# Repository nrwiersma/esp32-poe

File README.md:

# ESP32 PoE

`ESP32 PoE` is an ESP32 dev-kit with a W5500 LAN with PoE.

Features:

* W5500 Ethernet
* PoE (Power over Ethernet) 802.3af 7W
* ESP32 S3 WROOM-1

## Tasmota Configuration

To configure Tasmota for the ESP32 PoE board, you can use the following template:

```
{"NAME":"ESP32PoE","GPIO":[0,1,1,1,1,1,1,1,0,5536,5600,704,672,736,5568,1,1,1,1,1,1,0,0,0,1,1,1,1,1,1,1,1,1,1,1,1,1,1],"FLAG":0,"BASE":1}
```

and set the `EthType` option to `8`.

Optionally you can disable WiFi by setting `Wifi` option to `0` in the consoleSt.

## BOM

See the [Interactive BOM](https://htmlpreview.github.io/?https://github.com/nrwiersma/esp32-poe/blob/main/bom/ibom.html) [(provided by InteractiveHtmlBom)
](https://github.com/openscopeproject/InteractiveHtmlBom).

## Why

When dealing with IoT devices, you often want to place them in locations where power outlets are not readily available. 
Power over Ethernet (PoE) allows you to power devices through the same Ethernet cable used for data transmission, 
simplifying installation and reducing cable clutter. It also allows for centralized power management, 
making it easier to monitor and control the power supply to multiple devices.

## Changelog

#### v0.1.0

* Initial schematic and board

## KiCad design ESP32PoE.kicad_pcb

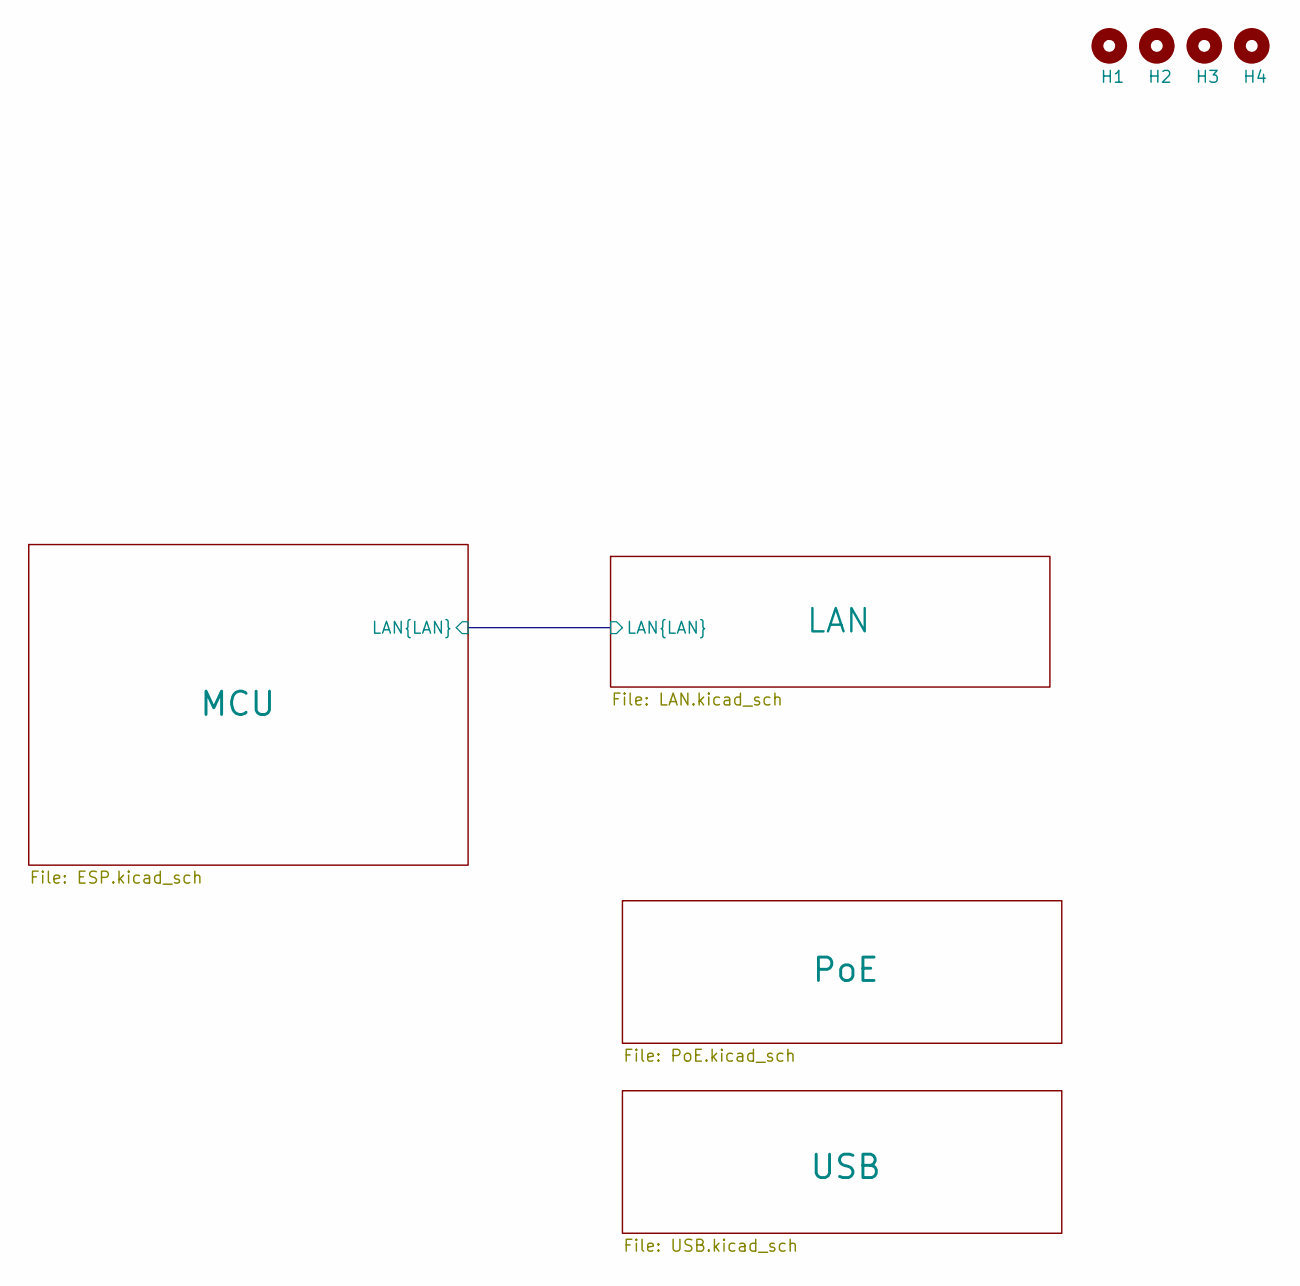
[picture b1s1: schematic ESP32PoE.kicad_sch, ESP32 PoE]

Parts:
H1, H2, H3, H4: MountingHole; MountingHole_2.2mm_M2

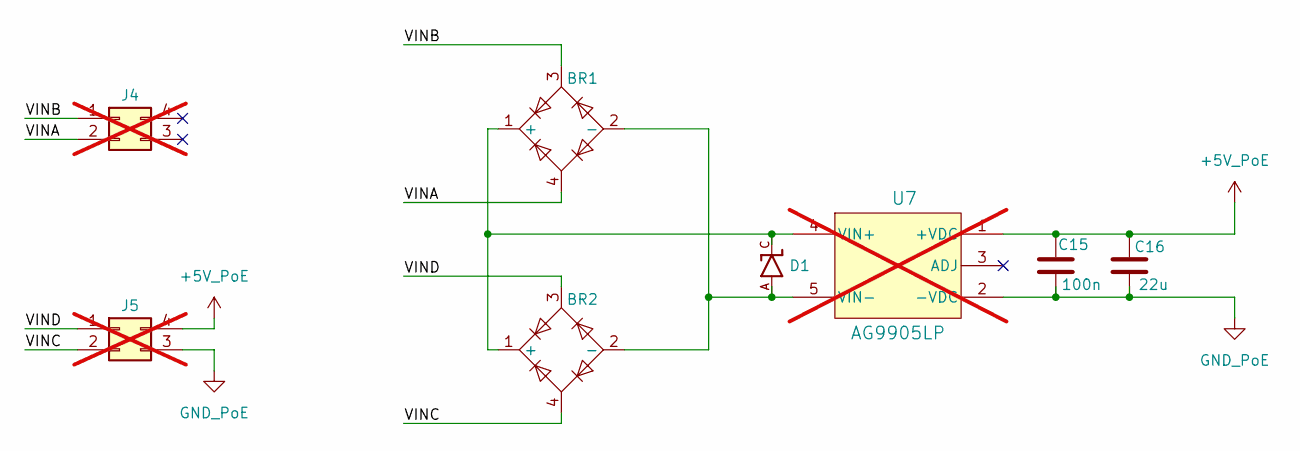
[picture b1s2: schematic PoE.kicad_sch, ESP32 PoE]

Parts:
BR1, BR2: MB110S; MPN MB110S; JLCPCB Part # C94545
C15: 100n; C_0402_1005Metric; MPN CL05B104KO5NNNC; JLCPCB Part # C1525
C16: 22u; C_0805_2012Metric; MPN CL21A226KPCLRNC; JLCPCB Part # C318688
D1: SMAJ58A; D_SMAJ58A; MPN SMAJ58A; JLCPCB Part # C151246
J4, J5: Conn_02x02_Counter_Clockwise; PinSocket_2x02_P2.54mm_Vertical; not fitted
U7: AG9905LP; POE_AG9905LP; MPN AG9905LP; not fitted

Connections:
+5V_PoE: C15.2, C16.1, J5.4, U7.1 (+VDC)
/PoE/VINA: BR1.4, J4.2
/PoE/VINB: BR1.3, J4.1
/PoE/VINC: BR2.4, J5.2
/PoE/VIND: BR2.3, J5.1
GND_PoE: C15.1, C16.2, J5.3, U7.2 (-VDC)
unnamed: BR1.1 (+), BR2.1 (+), D1.C, U7.4 (VIN+)
unnamed: BR1.2 (-), BR2.2 (-), D1.A, U7.5 (VIN-)

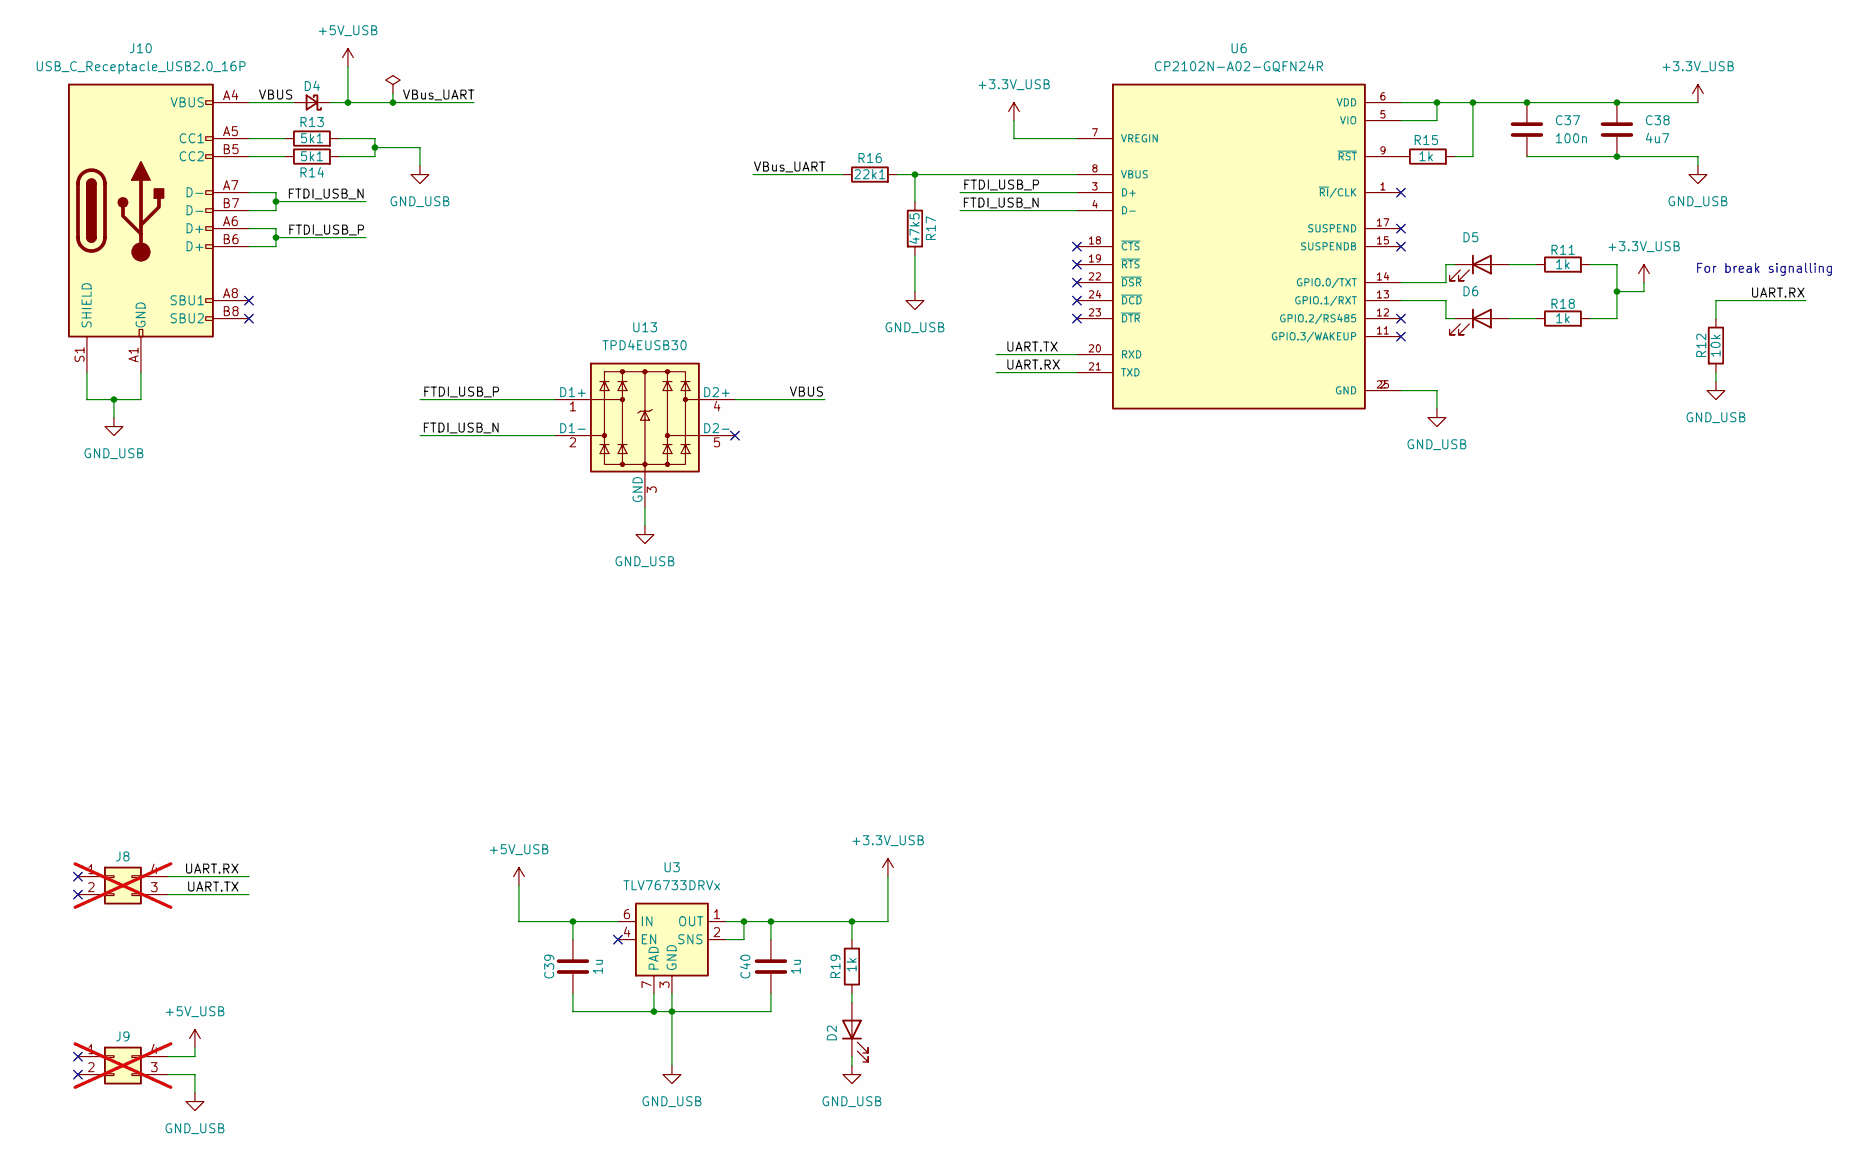
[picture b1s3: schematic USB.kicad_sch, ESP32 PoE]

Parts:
C37: 100n; C_0402_1005Metric; MPN CL05B104KO5NNNC; JLCPCB Part # C1525
C38: 4u7; C_0402_1005Metric; MPN CL05A475MO5NUNC; JLCPCB Part # C318563
C39, C40: 1u; C_0402_1005Metric; MPN CL05A105KP5NNNC; JLCPCB Part # C14445
D2: LED; LED_0603_1608Metric; MPN LTST-C191KRKT; JLCPCB Part # C125099
D4: D_Schottky_Small; D_0402_1005Metric; MPN CDBQR0130L-HF; JLCPCB Part # C2886014
D5, D6: LED; LED_0603_1608Metric; MPN LTST-C191KFKT; JLCPCB Part # C160478
J8, J9: Conn_02x02_Counter_Clockwise; PinSocket_2x02_P2.54mm_Vertical; not fitted
J10: USB_C_Receptacle_USB2.0_16P; USB_C_Receptacle_HRO_TYPE-C-31-M-12; MPN TYPE-C-31-M-12; JLCPCB Part # C165948
R11, R15, R18, R19: 1k; R_0402_1005Metric; MPN RK73H1ETTP1001F; JLCPCB Part # C131360
R12: 10k; R_0402_1005Metric; MPN CR0402-FX-1002GLF; JLCPCB Part # C202396
R13, R14: 5k1; R_0402_1005Metric; MPN RC0402FR-075K1L; JLCPCB Part # C105872
R16: 22k1; R_0402_1005Metric; MPN CR0402-FX-2212GLF; JLCPCB Part # C2085292
R17: 47k5; R_0402_1005Metric; MPN FRC0402F4752TS; JLCPCB Part # C2930010
U3: TLV76733DRVx; WSON-6-1EP_2x2mm_P0.65mm_EP1x1.6mm_ThermalVias; MPN TLV76733DRVR; JLCPCB Part # C2848334
U6: CP2102N-A02-GQFN24R; CP2102-A02-GQ-QFN-50P; MPN CP2102N-A02-GQFN24R; JLCPCB Part # C969151
U13: TPD4EUSB30; TPD4EUSB30_USON-10; MPN TPD4EUSB30DQAR; JLCPCB Part # C90627

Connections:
+3.3V_USB: C37.2, C38.1, C40.1, R11.2, R15.2, R18.2, R19.2, U3.1 (OUT), U3.2 (SNS), U6.5 (VIO), U6.6 (VDD), U6.7 (VREGIN)
+5V_USB: C39.1, D4.1 (K), J9.4, R16.1, U3.6 (IN)
/USB/FTDI_USB_N: J10.A7 (D-), J10.B7 (D-), U6.4 (D-), U13.2 (D1-), U13.9
/USB/FTDI_USB_P: J10.A6 (D+), J10.B6 (D+), U6.3 (D+), U13.1 (D1+), U13.10
/USB/UART.RX: J8.4, R12.1, U6.21 (TXD)
/USB/UART.TX: J8.3, U6.20 (RXD)
/USB/VBUS: D4.2 (A), J10.A4 (VBUS), J10.A9 (VBUS), J10.B4 (VBUS), J10.B9 (VBUS), U13.4 (D2+), U13.7
GND_USB: C37.1, C38.2, C39.2, C40.2, D2.1 (K), J9.3, J10.A1 (GND), J10.A12 (GND), J10.B1 (GND), J10.B12 (GND), J10.S1 (SHIELD), R12.2, R13.2, R14.2, R17.2, U3.3 (GND), U3.5 (GND), U3.7 (PAD), U6.2 (GND), U6.25 (GND), U13.3 (GND), U13.8 (GND)
unnamed: D2.2 (A), R19.1
unnamed: D5.2 (A), R11.1
unnamed: D5.1 (K), U6.14 (GPIO.0/TXT)
unnamed: D6.2 (A), R18.1
unnamed: D6.1 (K), U6.13 (GPIO.1/RXT)
unnamed: J10.A5 (CC1), R13.1
unnamed: J10.B5 (CC2), R14.1
unnamed: R16.2, R17.1, U6.8 (VBUS)
unnamed: R15.1, U6.9 (~RST)

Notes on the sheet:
For break signalling

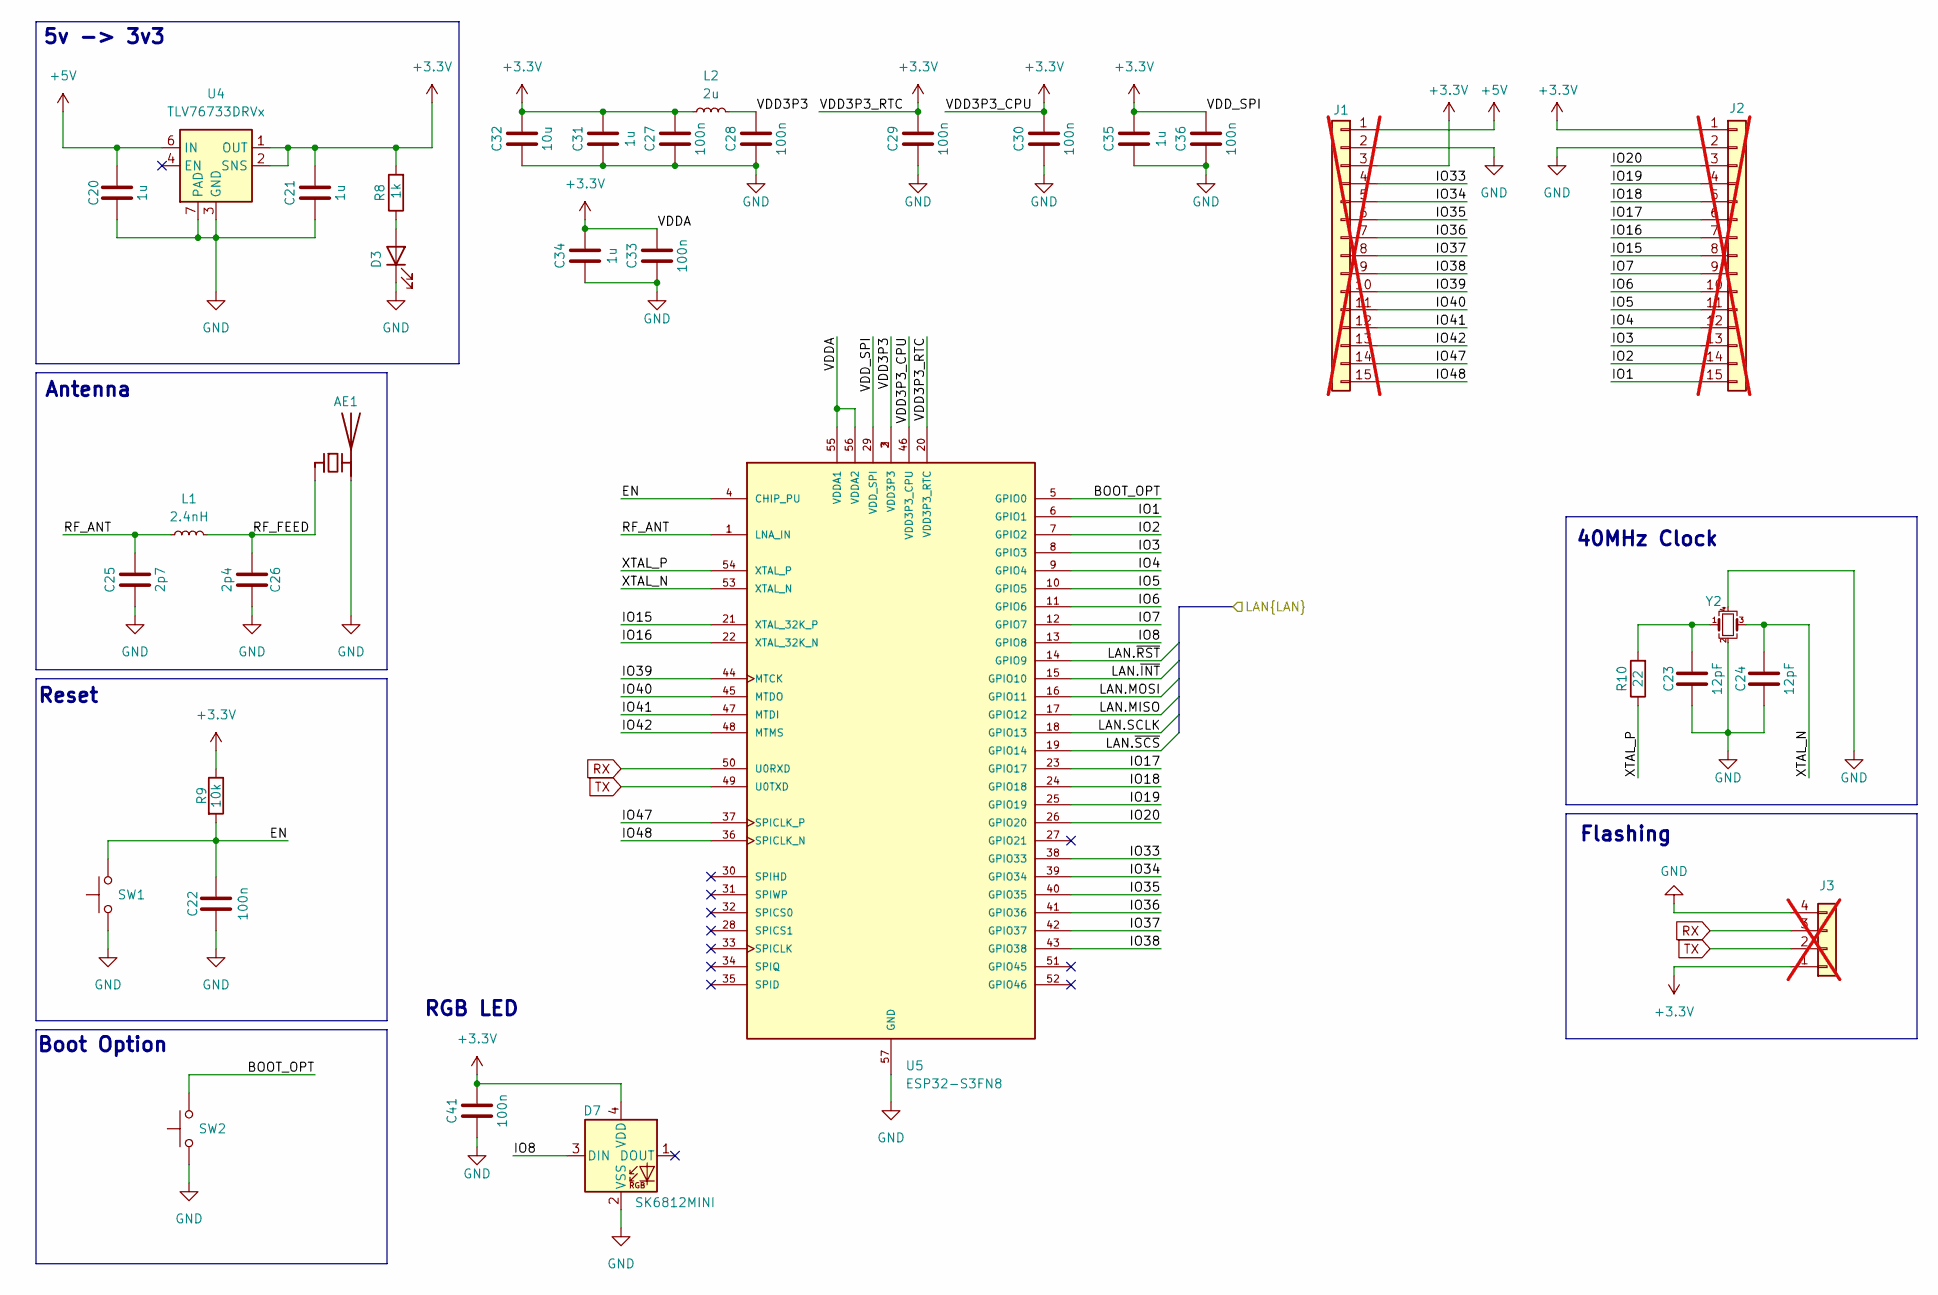
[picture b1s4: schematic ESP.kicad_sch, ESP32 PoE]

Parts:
AE1: Ant_RFECA3216060A1T_1206; Ant_RFECA3216060A1T; MPN RFECA3216060A1T; JLCPCB Part # C127620
C20, C21, C31, C34, C35: 1u; C_0402_1005Metric; MPN CL05A105KP5NNNC; JLCPCB Part # C14445
C22, C27, C28, C29, C30, C33, C36, C41: 100n; C_0402_1005Metric; MPN CL05B104KO5NNNC; JLCPCB Part # C1525
C23, C24: 12pF; C_0402_1005Metric; MPN CL05C120JB51PNC; JLCPCB Part # C472446
C25: 2p7; C_0402_1005Metric; MPN CL05C2R7BB5NNNC; JLCPCB Part # C159805
C26: 2p4; C_0402_1005Metric; MPN CL05C2R4CB5NNNC; JLCPCB Part # C318575
C32: 10u; C_0402_1005Metric; MPN CL05A106MP5NUNC; JLCPCB Part # C315248
D3: LED; LED_0603_1608Metric; MPN LTST-C191KRKT; JLCPCB Part # C125099
D7: SK6812MINI; LED_SK6812MINI; MPN SK6812MINI-HS; JLCPCB Part # C2922787
J1, J2: Conn_01x15_Pin; PinHeader_1x15_P2.54mm_Vertical; not fitted
J3: Conn_01x04_Pin; PinHeader_1x04_P2.54mm_Vertical; not fitted
L1: 2.4nH; L_0402_1005Metric; MPN MLG1005S2N4BT000; JLCPCB Part # C275281
L2: 2u; L_0402_1005Metric; MPN MLG1005S2N0BT000; JLCPCB Part # C76769
R8: 1k; R_0402_1005Metric; MPN RK73H1ETTP1001F; JLCPCB Part # C131360
R9: 10k; R_0402_1005Metric; MPN CR0402-FX-1002GLF; JLCPCB Part # C202396
R10: 22; R_0402_1005Metric; MPN RC0402FR-0722RL; JLCPCB Part # C114765
SW1, SW2: SW_Push; SW_PTS815SJM250SMTRLFS; MPN SKRPACE010; JLCPCB Part # C139797
U4: TLV76733DRVx; WSON-6-1EP_2x2mm_P0.65mm_EP1x1.6mm_ThermalVias; MPN TLV76733DRVR; JLCPCB Part # C2848334
U5: ESP32-S3FN8; MCU_ESP32-S3FN8; MPN ESP32-S3FN8; JLCPCB Part # C2913196
Y2: ECS-400-10-37B2-CKM-TR; Oscillator_ECS_400-10-37B2-CKM-TR; MPN ECS-400-10-37B2-CKM-TR; JLCPCB Part # C5371760

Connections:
+3.3V: C21.1, C27.1, C29.1, C30.1, C31.1, C32.1, C33.1, C34.1, C35.1, C36.1, C41.1, D7.4 (VDD), J1.3, J2.1, J3.1, L2.1, R8.2, R9.1, U4.1 (OUT), U4.2 (SNS), U5.20 (VDD3P3_RTC), U5.29 (VDD_SPI), U5.46 (VDD3P3_CPU), U5.55 (VDDA1), U5.56 (VDDA2); also elsewhere on the board
+5V: C20.1, J1.1, U4.6 (IN); also elsewhere on the board
/LAN/LAN.MISO: U5.17 (GPIO12); also elsewhere on the board
/LAN/LAN.MOSI: U5.16 (GPIO11); also elsewhere on the board
/LAN/LAN.SCLK: U5.18 (GPIO13); also elsewhere on the board
/LAN/LAN.~INT: U5.15 (GPIO10); also elsewhere on the board
/LAN/LAN.~RST: U5.14 (GPIO9); also elsewhere on the board
/LAN/LAN.~SCS: U5.19 (GPIO14); also elsewhere on the board
/MCU/BOOT_OPT: SW2.2, U5.5 (GPIO0)
/MCU/EN: C22.1, R9.2, SW1.2, U5.4 (CHIP_PU)
/MCU/IO1: J2.15, U5.6 (GPIO1)
/MCU/IO2: J2.14, U5.7 (GPIO2)
/MCU/IO3: J2.13, U5.8 (GPIO3)
/MCU/IO4: J2.12, U5.9 (GPIO4)
/MCU/IO5: J2.11, U5.10 (GPIO5)
/MCU/IO6: J2.10, U5.11 (GPIO6)
/MCU/IO7: J2.9, U5.12 (GPIO7)
/MCU/IO8: D7.3 (DIN), U5.13 (GPIO8)
/MCU/IO15: J2.8, U5.21 (XTAL_32K_P)
/MCU/IO16: J2.7, U5.22 (XTAL_32K_N)
/MCU/IO17: J2.6, U5.23 (GPIO17)
/MCU/IO18: J2.5, U5.24 (GPIO18)
/MCU/IO19: J2.4, U5.25 (GPIO19)
/MCU/IO20: J2.3, U5.26 (GPIO20)
/MCU/IO33: J1.4, U5.38 (GPIO33)
/MCU/IO34: J1.5, U5.39 (GPIO34)
/MCU/IO35: J1.6, U5.40 (GPIO35)
/MCU/IO36: J1.7, U5.41 (GPIO36)
/MCU/IO37: J1.8, U5.42 (GPIO37)
/MCU/IO38: J1.9, U5.43 (GPIO38)
/MCU/IO39: J1.10, U5.44 (MTCK)
/MCU/IO40: J1.11, U5.45 (MTDO)
/MCU/IO41: J1.12, U5.47 (MTDI)
/MCU/IO42: J1.13, U5.48 (MTMS)
/MCU/IO47: J1.14, U5.37 (SPICLK_P)
/MCU/IO48: J1.15, U5.36 (SPICLK_N)
/MCU/RF_ANT: C25.1, L1.1, U5.1 (LNA_IN)
/MCU/RF_FEED: AE1.1 (FEED), C26.2, L1.2
/MCU/VDD3P3: C28.1, L2.2, U5.2 (VDD3P3), U5.3 (VDD3P3)
/MCU/XTAL_N: C24.1, U5.53 (XTAL_N), Y2.3
/MCU/XTAL_P: R10.1, U5.54 (XTAL_P)
GND: AE1.2 (PCB_Trace), C20.2, C21.2, C22.2, C23.2, C24.2, C25.2, C26.1, C27.2, C28.2, C29.2, C30.2, C31.2, C32.2, C33.2, C34.2, C35.2, C36.2, C41.2, D3.1 (K), D7.2 (VSS), J1.2, J2.2, J3.4, SW1.1, SW2.1, U4.3 (GND), U4.5 (GND), U4.7 (PAD), U5.57 (GND), Y2.2, Y2.4; also elsewhere on the board
unnamed: C23.1, R10.2, Y2.1
unnamed: D3.2 (A), R8.1
RX: J3.3, U5.50 (U0RXD); also elsewhere on the board
TX: J3.2, U5.49 (U0TXD); also elsewhere on the board

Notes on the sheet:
Antenna
Reset
5v -> 3v3
Flashing
Boot Option
RGB LED
40MHz Clock

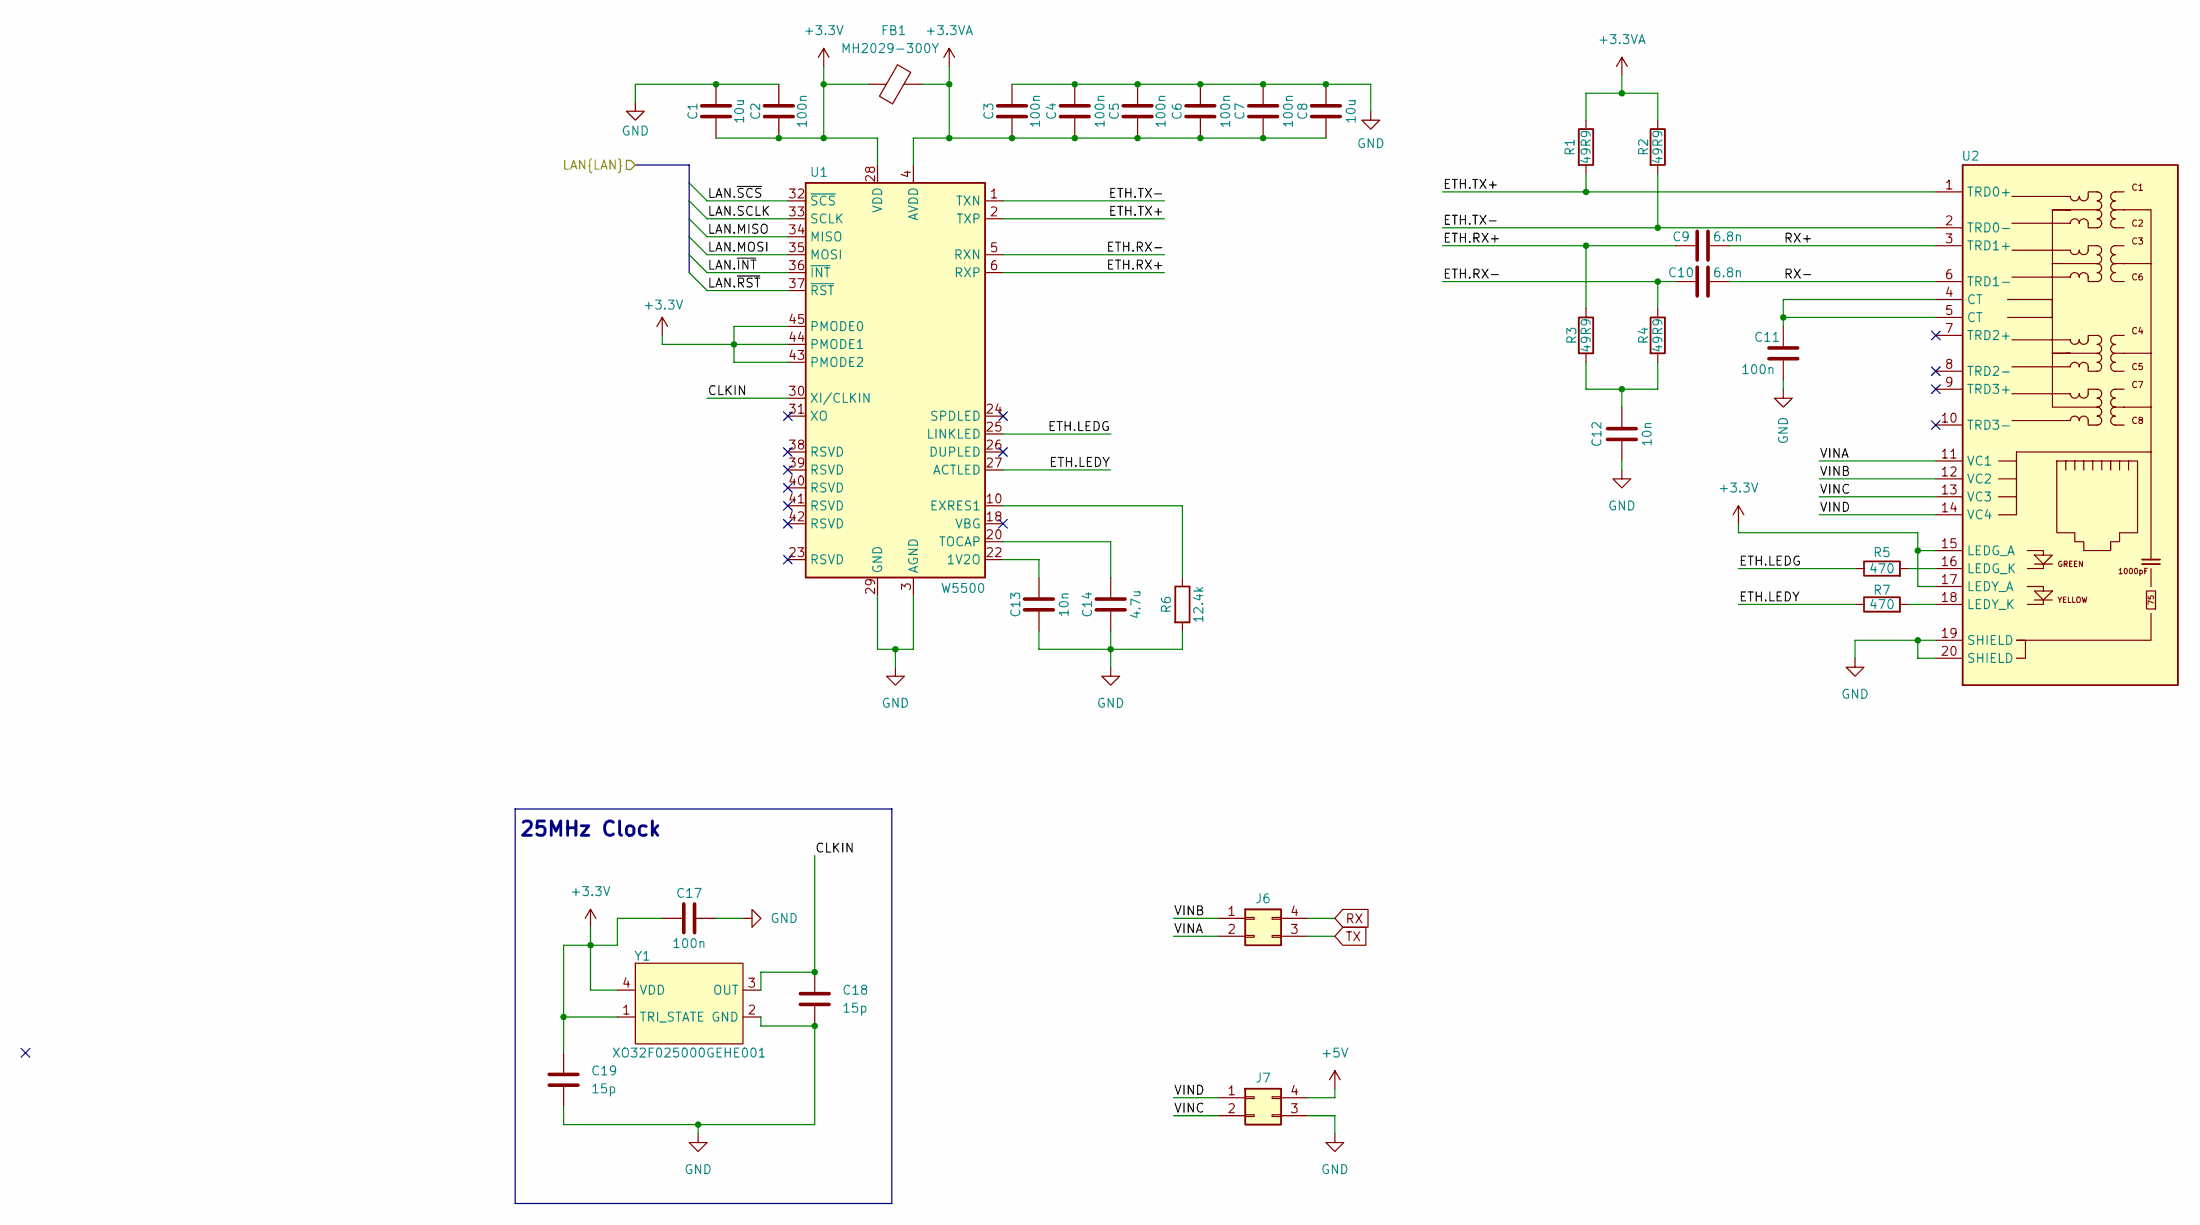
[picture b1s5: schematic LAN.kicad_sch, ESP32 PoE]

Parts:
C1, C8: 10u; C_0402_1005Metric; MPN CL05A106MP5NUNC; JLCPCB Part # C315248
C2, C3, C4, C5, C6, C7, C11, C17: 100n; C_0402_1005Metric; MPN CL05B104KO5NNNC; JLCPCB Part # C1525
C9, C10: 6.8n; C_0603_1608Metric; MPN CC0603KRX7R0BB682; JLCPCB Part # C576854
C12, C13: 10n; C_0402_1005Metric; MPN CL05B103KA5NNNC; JLCPCB Part # C318576
C14: 4.7u; C_0402_1005Metric; MPN CL05B472KB5NNNC; JLCPCB Part # C84705
C18, C19: 15p; C_0402_1005Metric; MPN CL05C150JB5NNNC; JLCPCB Part # C86285
FB1: MH2029-300Y; FB_0805_2012Metric; MPN MH2029-300Y; JLCPCB Part # C840593
J6, J7: Conn_02x02_Counter_Clockwise; Conn_PinHeader_2x02_P2.54mm_Vertical; MPN PZ254V-12-4P; JLCPCB Part # C492419
R1, R2, R3, R4: 49R9; R_0402_1005Metric; MPN AC0402FR-7W49R9L; JLCPCB Part # C5936310
R5, R7: 470; R_0402_1005Metric; MPN RC0402FR-7W470RL; JLCPCB Part # C606172
R6: 12.4k; R_0402_1005Metric; MPN RC0402FR-0712K4L; JLCPCB Part # C138060
U1: W5500; LQFP-48_7x7mm_P0.5mm; MPN W5500; JLCPCB Part # C32843
U2: MagJack-A70-112-331N126; RJ45_USAKRO_DGUK111Q334AB2A2DP057; MPN DGUK111Q334AB2A2DP057; JLCPCB Part # C19725175
Y1: XO32F025000GEHE001; Oscillator_TDK_SMD3225-4P; MPN XO32F025000GEHE001; JLCPCB Part # C20607963

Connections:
+3.3V: C1.1, C2.1, C17.2, C19.2, FB1.1, U1.28 (VDD), U1.43 (PMODE2), U1.44 (PMODE1), U1.45 (PMODE0), U2.15 (LEDG_A), U2.17 (LEDY_A), Y1.1 (TRI_STATE), Y1.4 (VDD); also elsewhere on the board
+3.3VA: C3.1, C4.1, C5.1, C6.1, C7.1, C8.1, FB1.2, R1.1, R2.1, U1.4 (AVDD), U1.8 (AVDD), U1.11 (AVDD), U1.15 (AVDD), U1.17 (AVDD), U1.21 (AVDD)
+5V: J7.4; also elsewhere on the board
/LAN/CLKIN: C18.1, U1.30 (XI/CLKIN), Y1.3 (OUT)
/LAN/ETH.LEDG: R5.1, U1.25 (LINKLED)
/LAN/ETH.LEDY: R7.1, U1.27 (ACTLED)
/LAN/ETH.RX+: C9.1, R3.1, U1.6 (RXP)
/LAN/ETH.RX-: C10.1, R4.1, U1.5 (RXN)
/LAN/ETH.TX+: R1.2, U1.2 (TXP), U2.1 (TRD0+)
/LAN/ETH.TX-: R2.2, U1.1 (TXN), U2.2 (TRD0-)
/LAN/LAN.MISO: U1.34 (MISO); also elsewhere on the board
/LAN/LAN.MOSI: U1.35 (MOSI); also elsewhere on the board
/LAN/LAN.SCLK: U1.33 (SCLK); also elsewhere on the board
/LAN/LAN.~INT: U1.36 (~INT); also elsewhere on the board
/LAN/LAN.~RST: U1.37 (~RST); also elsewhere on the board
/LAN/LAN.~SCS: U1.32 (~SCS); also elsewhere on the board
/LAN/RX+: C9.2, U2.3 (TRD1+)
/LAN/RX-: C10.2, U2.6 (TRD1-)
/LAN/VINA: J6.2, U2.11 (VC1)
/LAN/VINB: J6.1, U2.12 (VC2)
/LAN/VINC: J7.2, U2.13 (VC3)
/LAN/VIND: J7.1, U2.14 (VC4)
GND: C1.2, C2.2, C3.2, C4.2, C5.2, C6.2, C7.2, C8.2, C11.2, C12.2, C13.2, C14.2, C17.1, C18.2, C19.1, J7.3, R6.2, U1.3 (AGND), U1.9 (AGND), U1.14 (AGND), U1.16 (AGND), U1.19 (AGND), U1.29 (GND), U1.48 (AGND), U2.19 (SHIELD), U2.20 (SHIELD), Y1.2 (GND); also elsewhere on the board
unnamed: C11.1, U2.4 (CT), U2.5 (CT)
unnamed: C12.1, R3.2, R4.2
unnamed: C13.1, U1.22 (1V2O)
unnamed: R6.1, U1.10 (EXRES1)
unnamed: C14.1, U1.20 (TOCAP)
unnamed: R5.2, U2.16 (LEDG_K)
unnamed: R7.2, U2.18 (LEDY_K)
RX: J6.4; also elsewhere on the board
TX: J6.3; also elsewhere on the board

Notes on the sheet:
25MHz Clock

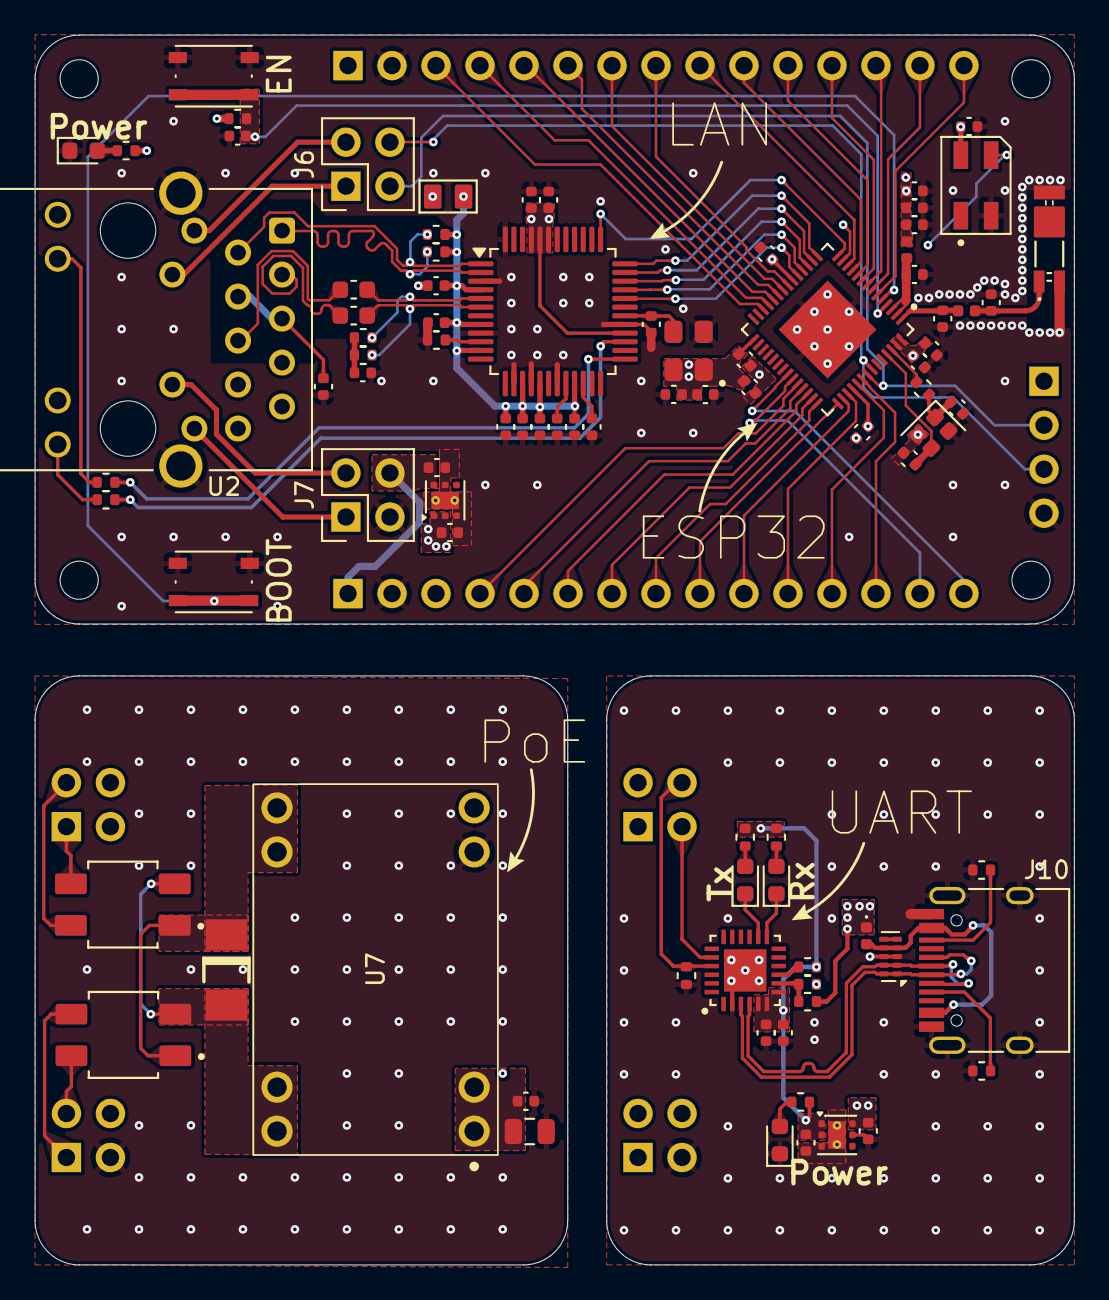
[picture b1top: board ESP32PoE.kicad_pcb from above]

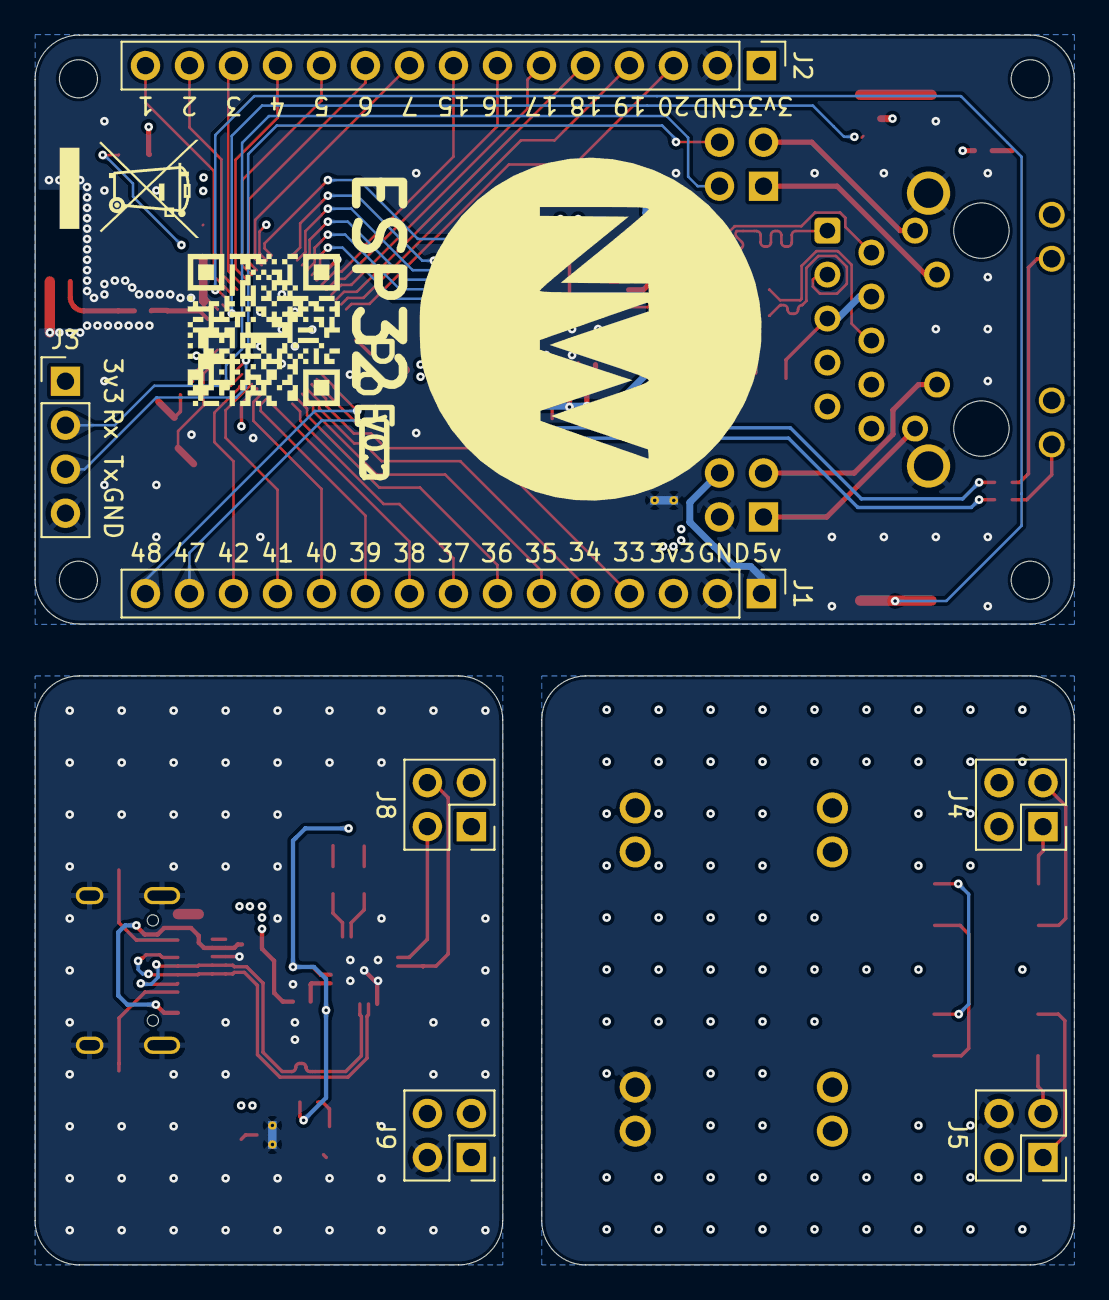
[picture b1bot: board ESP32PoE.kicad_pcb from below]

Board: 4 copper layers, 60.0 x 71.0 mm, 101 parts (9 on the bottom side), 92 nets.

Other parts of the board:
SS1: LOGO; Logo
SS3: WEEE-Logo_5.6x8mm_SilkScreen

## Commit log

2025-06-22 chore: intial commit
2025-06-22 wip: initial board
2025-06-22 feat: add QR code
2025-06-22 fix: board notes
2025-06-22 wip: minor adjustments
2025-06-26 feat: label poe
2025-06-26 fix: pin order
2025-06-27 fix: improve poe footprint
2025-07-23 feat: improve silkscreen
2025-07-24 feat: initial board (#1)
2025-08-06 chore: schematic PDF and iBOM
2025-08-26 chore: add README
2025-08-26 chore: add README (#2)
2025-11-11 feat: redesign to smaller form factor
2025-12-01 wip: mini form factor

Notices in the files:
README.md:
License: MIT
